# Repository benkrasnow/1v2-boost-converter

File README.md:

# 1v2-boost-converter
Schematics and PCB layout for a boost converter 0.9V minimum input, 30A maximum input current

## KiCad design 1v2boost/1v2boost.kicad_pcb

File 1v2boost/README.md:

# 1.2 V → 12 V / 20 W Boost Converter (KiCad 9)

Boost converter for an electromechanical cell: **0.9–1.6 V in (up to 28 A) →
12 V at 20 W**, biased from a separate low-current 12 V rail.

Open `1v2boost.kicad_pro` in KiCad 9. The project is **fully self-contained** —
every symbol and footprint lives in `lib/`, referenced through `${KIPRJMOD}`,
so no stock or external library is needed.

| | |
|---|---|
| Controller | TPS40210DGQ (not LM5155 — see below) |
| Gate driver | UCC27511A, 4 A/8 A — required, not optional |
| Topology | single-stage non-synchronous boost, 100 kHz |
| Efficiency | 89.2 % at 1.2 V, 84.0 % at the 0.9 V corner |
| Board | 2-layer, 2 oz copper, 150 × 100 mm |
| BOM | 41 line items, 60 fitted parts + 1 DNP |

## The two findings that shaped the design

**LM5155 cannot do this.** Its maximum duty cycle is spec'd at **90 % minimum**
(93 % typ) at 100 kHz. This converter needs D = 0.910 at nominal input and
0.937 at the 0.9 V corner. TPS40210 has no hard duty limit at all — only a
200 ns worst-case minimum off-time, giving D_max = 0.98.

**LM5122 (the synchronous, more efficient option) cannot do it either.** Its
current-sense common-mode range is 3 V–65 V, and in a boost that common mode
*is* the 1.2 V input. Only a ground-referenced low-side shunt works down here.

## Verification status

Checked with KiCad 10.0.5 (`kicad-cli`) on 2026-07-24:

| Check | Result |
|---|---|
| `sch erc` | **0 violations** |
| `pcb drc --schematic-parity` | **0 parity issues** — board matches schematic |
| `pcb drc` errors | 36 unconnected pads (see below) |
| `pcb drc` warnings | 9 dangling track stubs |
| clearance / shorts / holes / silk | **clean** |

## Read before fabricating

- **21 connections are still unrouted**, all small-signal, around the
  controller and the UVLO comparator. The generator refuses to emit copper
  that would violate clearance, so it leaves these as ratsnest rather than
  shipping near-shorts. **This board is not fabricable until they are
  routed** — open it in KiCad and finish them.
- **Take R2's sense connections at the finger tips, not the solder pads.** The
  shunt is a two-terminal part; its Kelvin behaviour comes entirely from the
  shape of the land pattern, and the two are the same net, so nothing will stop
  you attaching in the wrong place. See §7 of the design notes.

Full reasoning, loss budget, control-loop design and bring-up procedure:
**[docs/design-notes.md](docs/design-notes.md)**

## Regenerating

Everything is generated from `tools/netlist.py`, which is the single source of
truth for the circuit — the schematic, board and BOM cannot disagree with it.

```sh
python tools/build.py          # everything below, then ERC + DRC
```

`build.py` finds `kicad-cli` automatically (override with `KICAD_CLI`). It
runs the generators in order, fills the zones with KiCad's own filler, then
runs `validate.py`, ERC and DRC. Individual steps:

```sh
python tools/symbols.py        # lib/1v2boost.kicad_sym
python tools/footprints.py     # lib/1v2boost.pretty/
python tools/gen_schematic.py  # .kicad_sch, .kicad_pro, lib tables
python tools/gen_pcb.py        # .kicad_pcb  (reads KiCad's netlist export)
python tools/gen_bom.py        # bom/1v2boost-bom.csv
python tools/validate.py       # netlist round-trip + layer checks
python tools/design.py         # design report and margin checks
```

### How schematic changes reach the PCB

KiCad has no headless equivalent of Eeschema's **Update PCB from Schematic**
(F8) — no `kicad-cli sch update-pcb`, no `BOARD_NETLIST_UPDATER` in pcbnew's
Python, and the KiCad 10 IPC bindings are not installed. So `gen_pcb.py`
instead builds the board *from* `kicad-cli sch export netlist`, which is
KiCad's own authoritative reading of the schematic — net names, component
fields and DNP/BOM flags all come from there. The proof that it worked is
`pcb drc --schematic-parity` reporting **0 parity issues**; pressing F8 in
Eeschema should report nothing to change.

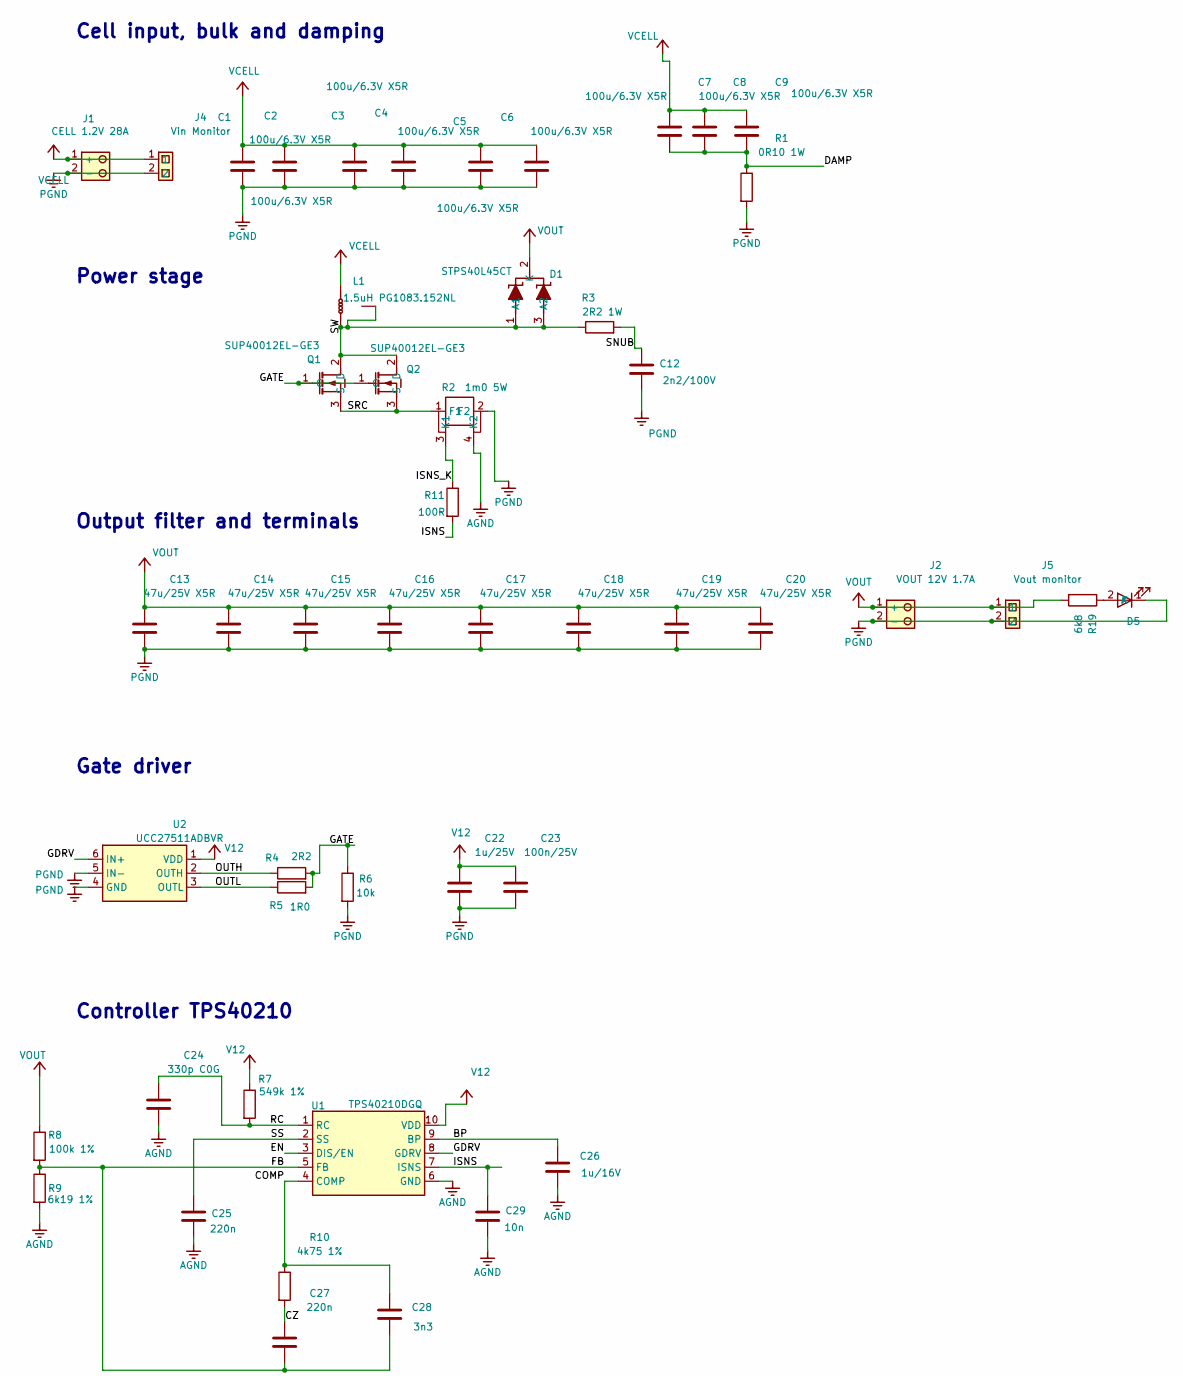
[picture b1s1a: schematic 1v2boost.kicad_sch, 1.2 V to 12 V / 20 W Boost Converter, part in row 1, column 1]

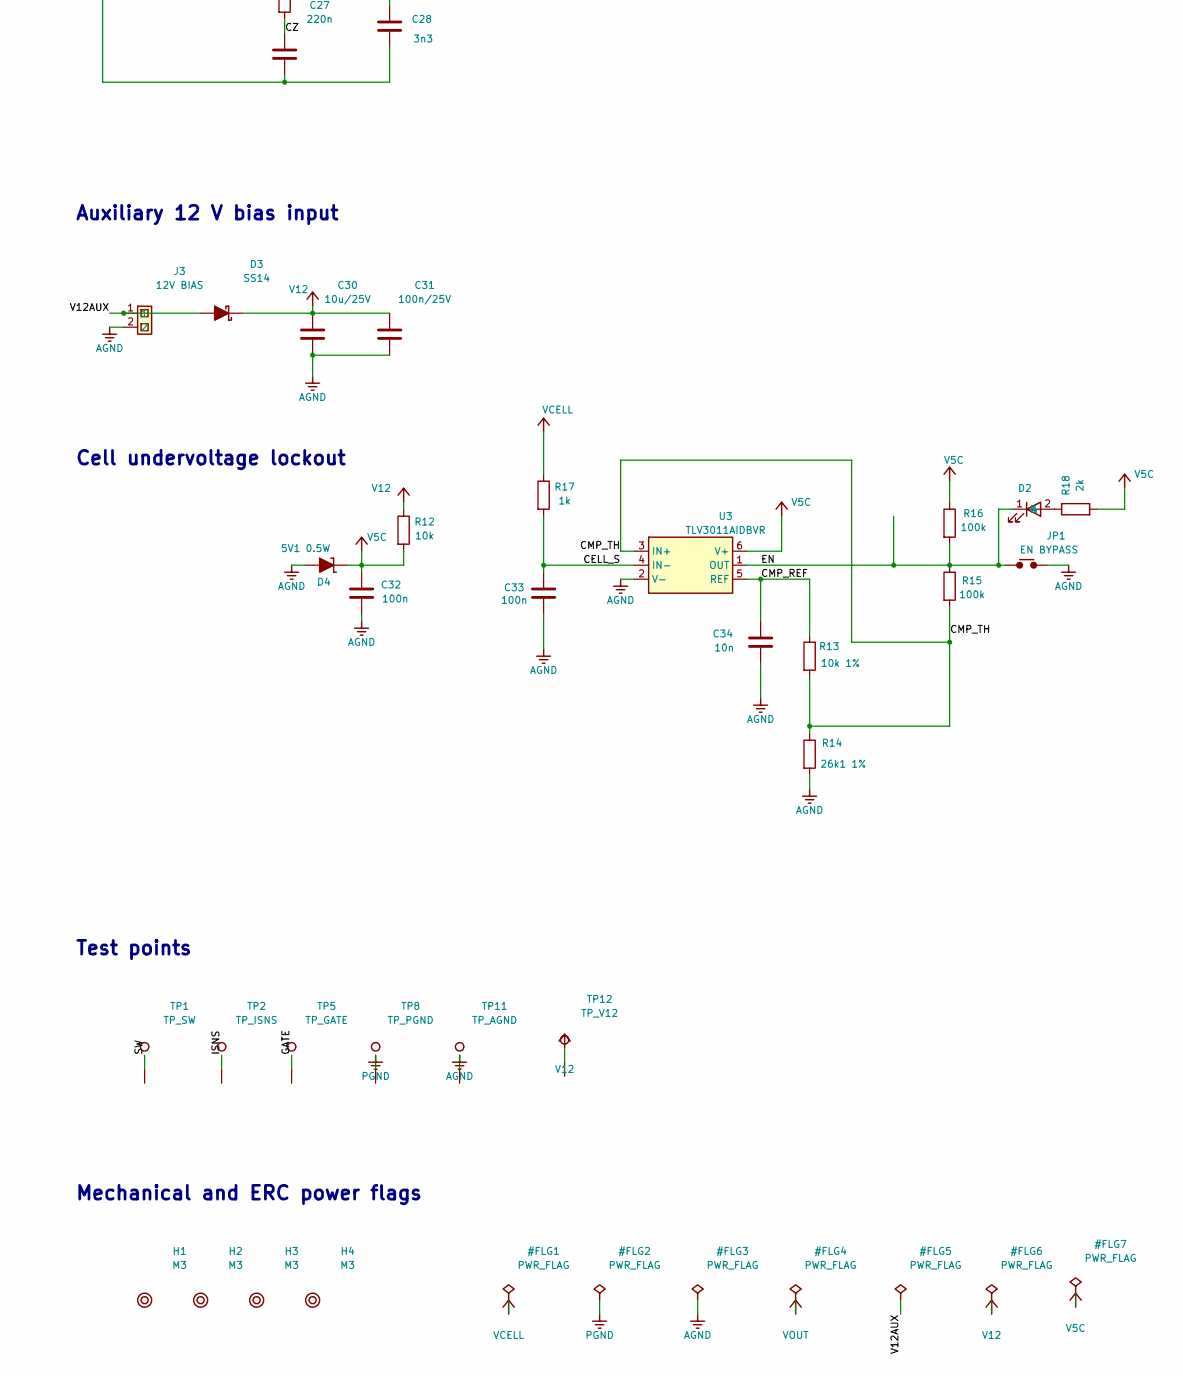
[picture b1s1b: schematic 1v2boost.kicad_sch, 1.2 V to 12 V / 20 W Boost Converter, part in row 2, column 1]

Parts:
C1, C2, C3, C4, C5, C6, C7, C8, C9: 100u/6.3V X5R; C_1210_3225Metric; MPN CL32A107MQVNNWE; Digi-Key P/N 1276-3366-1-ND
C12: 2n2/100V; C_1210_3225Metric; MPN C1210C222J1GACTU; Digi-Key P/N 399-C1210C222J1GACTUCT-ND
C13, C14, C15, C16, C17, C18, C19, C20: 47u/25V X5R; C_1210_3225Metric; MPN TMK325ABJ476MM-P; Digi-Key P/N 587-5479-1-ND
C22: 1u/25V; C_0805_2012Metric; MPN C0805C105K3RACTU; Digi-Key P/N 399-C0805C105K3RACTUCT-ND
C23, C31: 100n/25V; C_0603_1608Metric; MPN C0603C104K5RACTU; Digi-Key P/N 399-C0603C104K5RACTUCT-ND
C24: 330p C0G; C_0603_1608Metric; MPN CL10C331JB8NNNC; Digi-Key P/N 1276-1073-1-ND
C25, C27: 220n; C_0603_1608Metric; MPN GRM188R71H224KAC4D; Digi-Key P/N 490-12546-1-ND
C26: 1u/16V; C_0603_1608Metric; MPN C0603C105K4RACTU; Digi-Key P/N 399-C0603C105K4RACTUCT-ND
C28: 3n3; C_0603_1608Metric; MPN GCM1885C1H332FA16D; Digi-Key P/N 490-GCM1885C1H332FA16DCT-ND
C29: 10n; C_0603_1608Metric
C30: 10u/25V; C_1210_3225Metric; MPN C3225X7R1E106M250AC; Digi-Key P/N 445-1434-1-ND
C32, C33: 100n; C_0603_1608Metric; MPN C0603C104K5RACTU; Digi-Key P/N 399-C0603C104K5RACTUCT-ND
C34: 10n; C_0603_1608Metric; MPN CL10B103KB8NNNC; Digi-Key P/N 1276-1009-1-ND
D1: STPS40L45CT; TO-220-3_Vertical; MPN STPS40L45CT; Digi-Key P/N 497-7567-5-ND
D2, D5: LED_0603
D3: SS14; D_SMA; MPN SS14; Digi-Key P/N SS14CT-ND
D4: 5V1 0.5W; D_SOD-123; MPN MMSZ5231B-7-F; Digi-Key P/N MMSZ5231B-FDICT-ND
H1, H2, H3, H4: M3; MountingHole_3.2mm_M3
J1: CELL 1.2V 28A; SolderPad_Pair_Input_14x10mm
J2: VOUT 12V 1.7A; SolderPad_Pair_Output_8x6mm
J3: 12V BIAS; PinHeader_1x02_P2.54mm; MPN PREC002SAAN-RC; Digi-Key P/N 35-PREC002SAAN-RC-ND
J4: Vin Monitor; PinHeader_1x02_P2.54mm; MPN PREC002SAAN-RC; Digi-Key P/N 35-PREC002SAAN-RC-ND
J5: Vout monitor; PinHeader_1x02_P2.54mm; MPN PREC002SAAN-RC; Digi-Key P/N 35-PREC002SAAN-RC-ND
JP1: EN BYPASS; R_0805_2012Metric; MPN RC0805JR-070RL; Digi-Key P/N 311-0.0ARCT-ND
L1: 1.5uH PG1083.152NL; L_Pulse_PG1083; MPN PG1083.152NL; Digi-Key P/N 553-3164-ND
Q1, Q2: SUP40012EL-GE3; TO-220-3_Vertical; MPN SUP40012EL-GE3; Digi-Key P/N SUP40012EL-GE3-ND
R1: 0R10 1W; R_1210_3225Metric; MPN RCWE1210R100FKEA; Digi-Key P/N 541-4390-1-ND
R2: 1m0 5W; R_Shunt_2512_CSS2H; MPN CSS2H-2512R-1L00F; Digi-Key P/N CSS2H-2512R-1L00FCT-ND
R3: 2R2 1W; R_1210_3225Metric; MPN ESR25JZPJ2R2; Digi-Key P/N RHM2.2AXCT-ND
R4: 2R2; R_0805_2012Metric; MPN RC0805FR-072R2L; Digi-Key P/N 311-2.20CRCT-ND
R5: 1R0; R_0805_2012Metric; MPN RC0805FR-071RL; Digi-Key P/N 311-1.00CRCT-ND
R6: 10k; R_0805_2012Metric; MPN RC0805FR-0710KL; Digi-Key P/N 311-10.0KCRCT-ND
R7: 549k 1%; R_0603_1608Metric; MPN RC0603FR-07549KL; Digi-Key P/N 311-549KHRCT-ND
R8: 100k 1%; R_0603_1608Metric; MPN RC0603FR-07100KL; Digi-Key P/N 311-100KHRCT-ND
R9: 6k19 1%; R_0603_1608Metric; MPN ERJ-3EKF6191V; Digi-Key P/N P6.19KHCT-ND
R10: 4k75 1%; R_0603_1608Metric; MPN RC0603FR-074K75L; Digi-Key P/N 311-4.75KHRCT-ND
R11: 100R; R_0603_1608Metric; MPN RC0603FR-07100RL; Digi-Key P/N 311-100HRCT-ND
R12: 10k; R_0603_1608Metric; MPN RC0603FR-0710KL; Digi-Key P/N 311-10.0KHRCT-ND
R13: 10k 1%; R_0603_1608Metric; MPN RC0603FR-0710KL; Digi-Key P/N 311-10.0KHRCT-ND
R14: 26k1 1%; R_0603_1608Metric; MPN RC0603FR-0726K1L; Digi-Key P/N 311-26.1KHRCT-ND
R15, R16: 100k; R_0603_1608Metric; MPN RC0603FR-07100KL; Digi-Key P/N 311-100KHRCT-ND
R17: 1k; R_0603_1608Metric; MPN RC0603FR-071KL; Digi-Key P/N 311-1.00KHRCT-ND
R18: 2k; R_0603_1608Metric; MPN RC0603FR-07100KL; Digi-Key P/N 311-100KHRCT-ND
R19: 6k8; R_0603_1608Metric; MPN RC0603FR-07100KL; Digi-Key P/N 311-100KHRCT-ND
TP1: TP_SW; TestPoint_Pad_D1.5mm
TP2: TP_ISNS; TestPoint_Pad_D1.5mm
TP5: TP_GATE; TestPoint_Pad_D1.5mm
TP8: TP_PGND; TestPoint_Pad_D1.5mm
TP11: TP_AGND; TestPoint_Pad_D1.5mm
TP12: TP_V12; TestPoint_Pad_D1.5mm
U1: TPS40210DGQ; MSOP-10_3x3mm_P0.5mm; MPN TPS40210DGQR; Digi-Key P/N 296-26969-1-ND
U2: UCC27511ADBVR; SOT-23-6; MPN UCC27511ADBVR; Digi-Key P/N 296-49474-1-ND
U3: TLV3011AIDBVR; SOT-23-6; MPN TLV3011AIDBVR; Digi-Key P/N 296-39259-1-ND

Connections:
/BP: C26.1, U1.9 (BP)
/CELL_S: C33.1, R17.2, U3.4 (IN-)
/CMP_REF: C34.1, R13.1, U3.5 (REF)
/CMP_TH: R13.2, R14.1, R15.2, U3.3 (IN+)
/COMP: C28.1, R10.1, U1.4 (COMP)
/CZ: C27.1, R10.2
/DAMP: C7.2, C8.2, C9.2, R1.1
/EN: D2.1 (K), JP1.1, R15.1, R16.2, U1.3 (DIS/EN), U3.1 (OUT)
/FB: C27.2, C28.2, R8.2, R9.1, U1.5 (FB)
/GATE: Q1.1 (G), Q2.1 (G), R4.2, R5.2, R6.1, TP5.1 (1_1)
/GDRV: U1.8 (GDRV), U2.6 (IN+)
/ISNS: C29.1, R11.2, TP2.1 (1_1), U1.7 (ISNS)
/ISNS_K: R2.3 (K1), R11.1
/OUTH: R4.1, U2.2 (OUTH)
/OUTL: R5.1, U2.3 (OUTL)
/RC: C24.1, R7.2, U1.1 (RC)
/SNUB: C12.1, R3.2
/SRC: Q1.3 (S), Q2.3 (S), R2.1 (F1)
/SS: C25.1, U1.2 (SS)
/SW: D1.1 (A1), D1.3 (A2), L1.2, L1.3 (Mech_3), Q1.2 (D), Q2.2 (D), R3.1, TP1.1 (1_1)
/V12AUX: D3.2 (A), J3.1
AGND: C24.2, C25.2, C26.2, C29.2, C30.2, C31.2, C32.2, C33.2, C34.2, D4.2 (A), J3.2, JP1.2, R2.4 (K2), R9.2, R14.2, TP11.1 (1_1), U1.6 (GND), U3.2 (V-)
unnamed: D2.2 (A), R18.1
unnamed: D5.2 (A), R19.1
PGND: C1.2, C2.2, C3.2, C4.2, C5.2, C6.2, C12.2, C13.2, C14.2, C15.2, C16.2, C17.2, C18.2, C19.2, C20.2, C22.2, C23.2, D5.1 (K), J1.2 (-), J2.2 (-), J4.2, J5.2, R1.2, R2.2 (F2), R6.2, TP8.1 (1_1), U2.4 (GND), U2.5 (IN-)
V5C: C32.1, D4.1 (K), R12.2, R16.1, R18.2, U3.6 (V+)
V12: C22.1, C23.1, C30.1, C31.1, D3.1 (K), R7.1, R12.1, TP12.1 (1_1), U1.10 (VDD), U2.1 (VDD)
VCELL: C1.1, C2.1, C3.1, C4.1, C5.1, C6.1, C7.1, C8.1, C9.1, J1.1 (+), J4.1, L1.1, R17.1
VOUT: C13.1, C14.1, C15.1, C16.1, C17.1, C18.1, C19.1, C20.1, D1.2 (K), J2.1 (+), J5.1, R8.1, R19.2

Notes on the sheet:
Cell input, bulk and damping
Auxiliary 12 V bias input
Controller TPS40210
Gate driver
Power stage
Cell undervoltage lockout
Test points
Output filter and terminals
Mechanical and ERC power flags

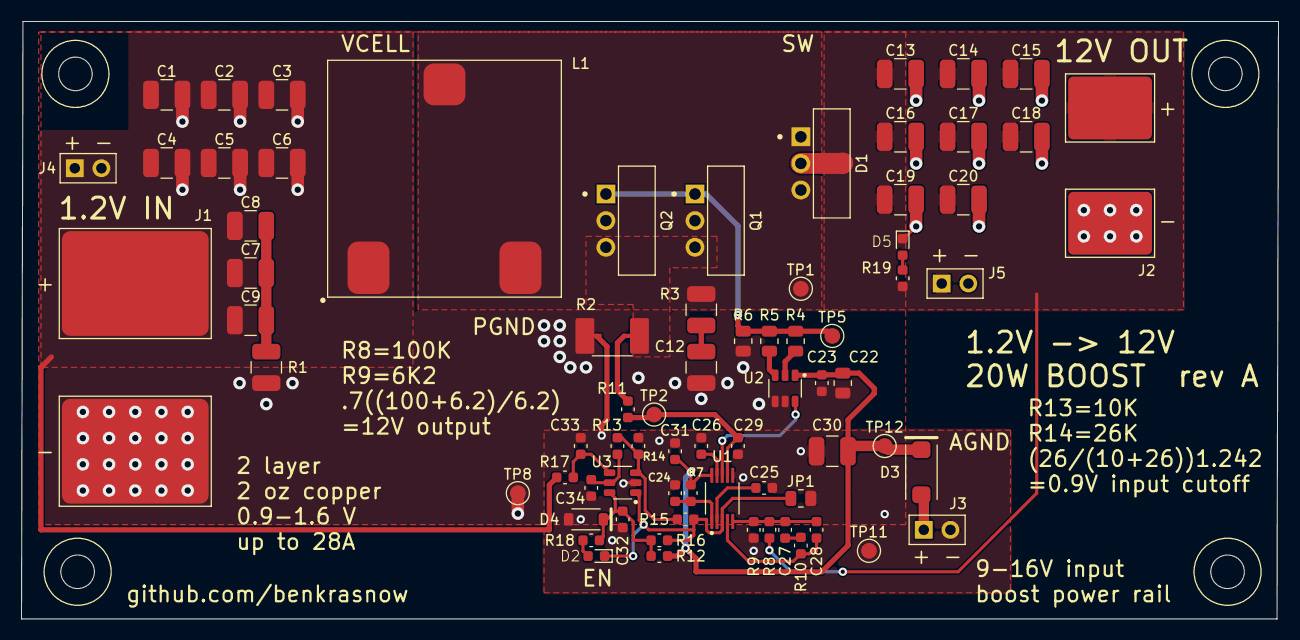
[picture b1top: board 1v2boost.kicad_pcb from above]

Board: 2 copper layers, 119.9 x 57.0 mm, 77 parts (0 on the bottom side), 29 nets.

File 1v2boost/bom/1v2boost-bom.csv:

Item,Qty,References,Value,Footprint,MPN,Manufacturer,Description,Digi-Key P/N,Fit,Notes
1,1,J1,CELL 1.2V 28A,SolderPad_Pair_Input_14x10mm,,,"Cell input, solder wire or braid directly",,Fit,
2,9,C1 C2 C3 C4 C5 C6 C7 C8 C9,100u/6.3V X5R,C_1210_3225Metric,CL32A107MQVNNWE,Samsung,Ceramic 100uF 6.3V X5R 1210,1276-3366-1-ND,Fit,
3,1,R1,0R10 1W,R_1210_3225Metric,RCWE1210R100FKEA,Vishay Dale,"0.1 ohm 1% 1W 1210 current sense, input filter damping",541-4390-1-ND,Fit,Damps the input filter against a low-impedance cell on long leads.
4,1,L1,1.5uH PG1083.152NL,L_Pulse_PG1083,PG1083.152NL,Pulse Electronics,1.5uH 1.4mohm Isat 52A Irms 40A round wire inductor,553-3164-ND,Fit,"Land pattern per Pulse datasheet P716.D: pads 1/2 4.00x5.00 mm on 14.50 mm centres, pad 3 4.00x4.00 mm at 17.50 mm. Pad 3 is a mounting tab - leave it unconnected. The core is conductive, so no exposed via may sit under the body (P716 note 10). DCR 1.4 mohm max, Isat 52 A, Irms 40 A. Dominant single loss in the design."
5,2,Q1 Q2,SUP40012EL-GE3,TO-220-3_Vertical,SUP40012EL-GE3,Vishay,N-MOSFET 40V 150A 1.49mohm logic level TO-220AB,SUP40012EL-GE3-ND,Fit,"Two in parallel. Logic level, Rds(on) 1.49 mohm typ at Vgs=10 V, Qgd 6.7 nC. Bolt both to a common heatsink - tabs are the SW node, so isolate from D1."
6,1,R2,1m0 5W,R_Shunt_2512_CSS2H,CSS2H-2512R-1L00F,Bourns,"1 mohm 5W current sense, 2512 (2-terminal)",CSS2H-2512R-1L00FCT-ND,Fit,"TWO-terminal part - the 4 pads are 2 terminals, tied in pairs (1+3, 2+4) per Bourns' own land pattern, where a 0.40 mm sense finger leaves each solder pad. Take ISNS_K and AGND at the finger tips, not the solder pads. Value is capped at 1.73 mohm by the slope compensation requirement (TPS40210 eq 19), which rules out every stocked value above 1 mohm. Raises the OC trip to 150 A."
7,1,D1,STPS40L45CT,TO-220-3_Vertical,STPS40L45CT,STMicroelectronics,"Schottky 45V 2x20A low drop, common cathode, TO-220AB",497-7567-5-ND,Fit,"Both halves paralleled. Tab is the cathode (VOUT), so it needs an insulating pad if it shares a heatsink with Q1/Q2."
8,1,R3,2R2 1W,R_1210_3225Metric,ESR25JZPJ2R2,Rohm,"2.2 ohm 5% 1W 1210, switch node snubber",RHM2.2AXCT-ND,Fit,Snubber. Tune on the bench - TO-220 lead inductance makes this necessary rather than optional.
9,1,C12,2n2/100V,C_1210_3225Metric,C1210C222J1GACTU,KEMET,"Ceramic 2.2nF 100V C0G 1210, snubber",399-C1210C222J1GACTUCT-ND,Fit,Snubber. Tune with R3.
10,8,C13 C14 C15 C16 C17 C18 C19 C20,47u/25V X5R,C_1210_3225Metric,TMK325ABJ476MM-P,Taiyo Yuden,Ceramic 47uF 25V X5R 1210,587-5479-1-ND,Fit,
11,1,J2,VOUT 12V 1.7A,SolderPad_Pair_Output_8x6mm,,,12 V output terminals,,Fit,
12,1,U2,UCC27511ADBVR,SOT-23-6,UCC27511ADBVR,Texas Instruments,"4A/8A single low-side gate driver, split outputs, SOT-23-6",296-49474-1-ND,Fit,"Mandatory, not optional: U1's own gate driver is only 400 mA and would cost ~2.2 W in switching loss driving 260 nC of gate charge."
13,1,R4,2R2,R_0805_2012Metric,RC0805FR-072R2L,Yageo,Turn-on gate resistor,311-2.20CRCT-ND,Fit,
14,1,R5,1R0,R_0805_2012Metric,RC0805FR-071RL,Yageo,Turn-off gate resistor,311-1.00CRCT-ND,Fit,
15,1,R6,10k,R_0805_2012Metric,RC0805FR-0710KL,Yageo,"Gate pulldown, holds FETs off when the driver is unpowered",311-10.0KCRCT-ND,Fit,
16,1,C22,1u/25V,C_0805_2012Metric,C0805C105K3RACTU,KEMET,Driver bulk decoupling,399-C0805C105K3RACTUCT-ND,Fit,
17,2,C23 C31,100n/25V,C_0603_1608Metric,C0603C104K5RACTU,KEMET,Driver HF decoupling,399-C0603C104K5RACTUCT-ND,Fit,
18,1,U1,TPS40210DGQ,MSOP-10_3x3mm_P0.5mm,TPS40210DGQR,Texas Instruments,"Wide-input non-synchronous boost controller, MSOP-10",296-26969-1-ND,Fit,"Controller. Chosen over LM5155 because it has no hard duty-cycle limit, only a 200 ns minimum off-time."
19,1,R7,549k 1%,R_0603_1608Metric,RC0603FR-07549KL,Yageo,"Oscillator timing resistor, 100 kHz",311-549KHRCT-ND,Fit,Sets 100 kHz with C24 = 330 pF. R*C*f ~= 18.0.
20,1,C24,330p C0G,C_0603_1608Metric,CL10C331JB8NNNC,Samsung,Oscillator timing capacitor,1276-1073-1-ND,Fit,
21,2,C25 C27,220n,C_0603_1608Metric,GRM188R71H224KAC4D,Murata,"Soft start, ~18 ms - long on purpose to limit cell inrush",490-12546-1-ND,Fit,
22,1,C26,1u/16V,C_0603_1608Metric,C0603C105K4RACTU,KEMET,BP regulator bypass,399-C0603C105K4RACTUCT-ND,Fit,
23,1,R8,100k 1%,R_0603_1608Metric,RC0603FR-07100KL,Yageo,"Feedback divider, upper",311-100KHRCT-ND,Fit,
24,1,R9,6k19 1%,R_0603_1608Metric,ERJ-3EKF6191V,Panasonic,"Feedback divider, lower",P6.19KHCT-ND,Fit,
25,1,R10,4k75 1%,R_0603_1608Metric,RC0603FR-074K75L,Yageo,Compensation resistor,311-4.75KHRCT-ND,Fit,
26,1,C28,3n3,C_0603_1608Metric,GCM1885C1H332FA16D,Murata,"HF pole, ~10 kHz",490-GCM1885C1H332FA16DCT-ND,Fit,
27,1,R11,100R,R_0603_1608Metric,RC0603FR-07100RL,Yageo,Current sense filter resistor,311-100HRCT-ND,Fit,
28,1,C29,1n,C_0603_1608Metric,CL10C102JB8NNNC,Samsung,Current sense filter capacitor,1276-1091-1-ND,Fit,
29,1,J3,12V BIAS,PinHeader_1x02_P2.54mm,PREC002SAAN-RC,Sullins,"Auxiliary 12 V bias input, ~60 mA",35-PREC002SAAN-RC-ND,Fit,
30,1,D3,SS14,D_SMA,SS14,onsemi,"Schottky 40V 1A, reverse polarity protection on the bias rail",SS14CT-ND,Fit,
31,1,C30,10u/25V,C_1210_3225Metric,C3225X7R1E106M250AC,TDK,Bias bulk,445-1434-1-ND,Fit,
32,1,R12,10k,R_0603_1608Metric,RC0603FR-0710KL,Yageo,"Zener dropper, ~690 uA",311-10.0KHRCT-ND,Fit,
33,1,D4,5V1 0.5W,D_SOD-123,MMSZ5231B-7-F,Diodes Incorporated,"5.1 V 0.5 W zener, comparator supply",MMSZ5231B-FDICT-ND,Fit,Creates the 5.1 V rail for U3 from the 12 V bias.
34,2,C32 C33,100n,C_0603_1608Metric,C0603C104K5RACTU,KEMET,Comparator supply bypass,399-C0603C104K5RACTUCT-ND,Fit,
35,1,U3,TLV3011AIDBVR,SOT-23-6,TLV3011AIDBVR,Texas Instruments,"Open-drain comparator with 1.242 V reference, SOT-23-6",296-39259-1-ND,Fit,"Cell undervoltage lockout - nothing in U1 watches the cell. Trips at 0.837 V, releases at 1.045 V. Max supply 5.5 V, hence the local zener rail from R12/D4."
36,1,R13,10k 1%,R_0603_1608Metric,RC0603FR-0710KL,Yageo,"UVLO threshold, upper",311-10.0KHRCT-ND,Fit,
37,1,R14,26k1 1%,R_0603_1608Metric,RC0603FR-0726K1L,Yageo,"UVLO threshold, lower",311-26.1KHRCT-ND,Fit,
38,2,R15 R16,100k,R_0603_1608Metric,RC0603FR-07100KL,Yageo,UVLO hysteresis,311-100KHRCT-ND,Fit,"UVLO hysteresis, and it sets BOTH thresholds - do not change it without re-running design.py uvlo_thresholds(). 207 mV must stay above the cell's I*R recovery step (~117 mV at 4 mohm)."
39,1,R17,1k,R_0603_1608Metric,RC0603FR-071KL,Yageo,Cell sense filter,311-1.00KHRCT-ND,Fit,
40,1,C34,10n,C_0603_1608Metric,CL10B103KB8NNNC,Samsung,Reference bypass,1276-1009-1-ND,Fit,
41,1,JP1,EN BYPASS,R_0805_2012Metric,RC0805JR-070RL,Yageo,"Solder jumper: fit to force enable, ignoring cell UVLO",311-0.0ARCT-ND,DNP,Do not fit. Fit only to bypass the cell UVLO and force enable.

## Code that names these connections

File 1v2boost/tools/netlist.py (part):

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--------------
PGND and AGND are deliberately separate nets. Their ONLY connection is at the
low-side terminal of the shunt R2: pin 2, the solder pad carrying the return
current, is PGND; pin 4, the sense finger on that same terminal, is AGND.

R2 is a two-terminal part, so pins 2 and 4 are one node - the footprint says
so with a net tie. The Kelvin behaviour is geometric, not electrical: the
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# recommended land pattern grows a 0.40 mm sense finger off each solder pad,
# running out past the body where it carries no load current. Pins 1 and 3 are
# one terminal and pins 2 and 4 are the other; the footprint says so with
# (net_tie_pad_groups "1, 3" "2, 4"). Keeping ISNS_K and AGND as their own nets
# is what makes "the sense trace starts at the finger" a rule the tools can
# check rather than a comment nobody reads.
add(ref="R2", symbol="R_Shunt_Kelvin", value="1m0 5W",
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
